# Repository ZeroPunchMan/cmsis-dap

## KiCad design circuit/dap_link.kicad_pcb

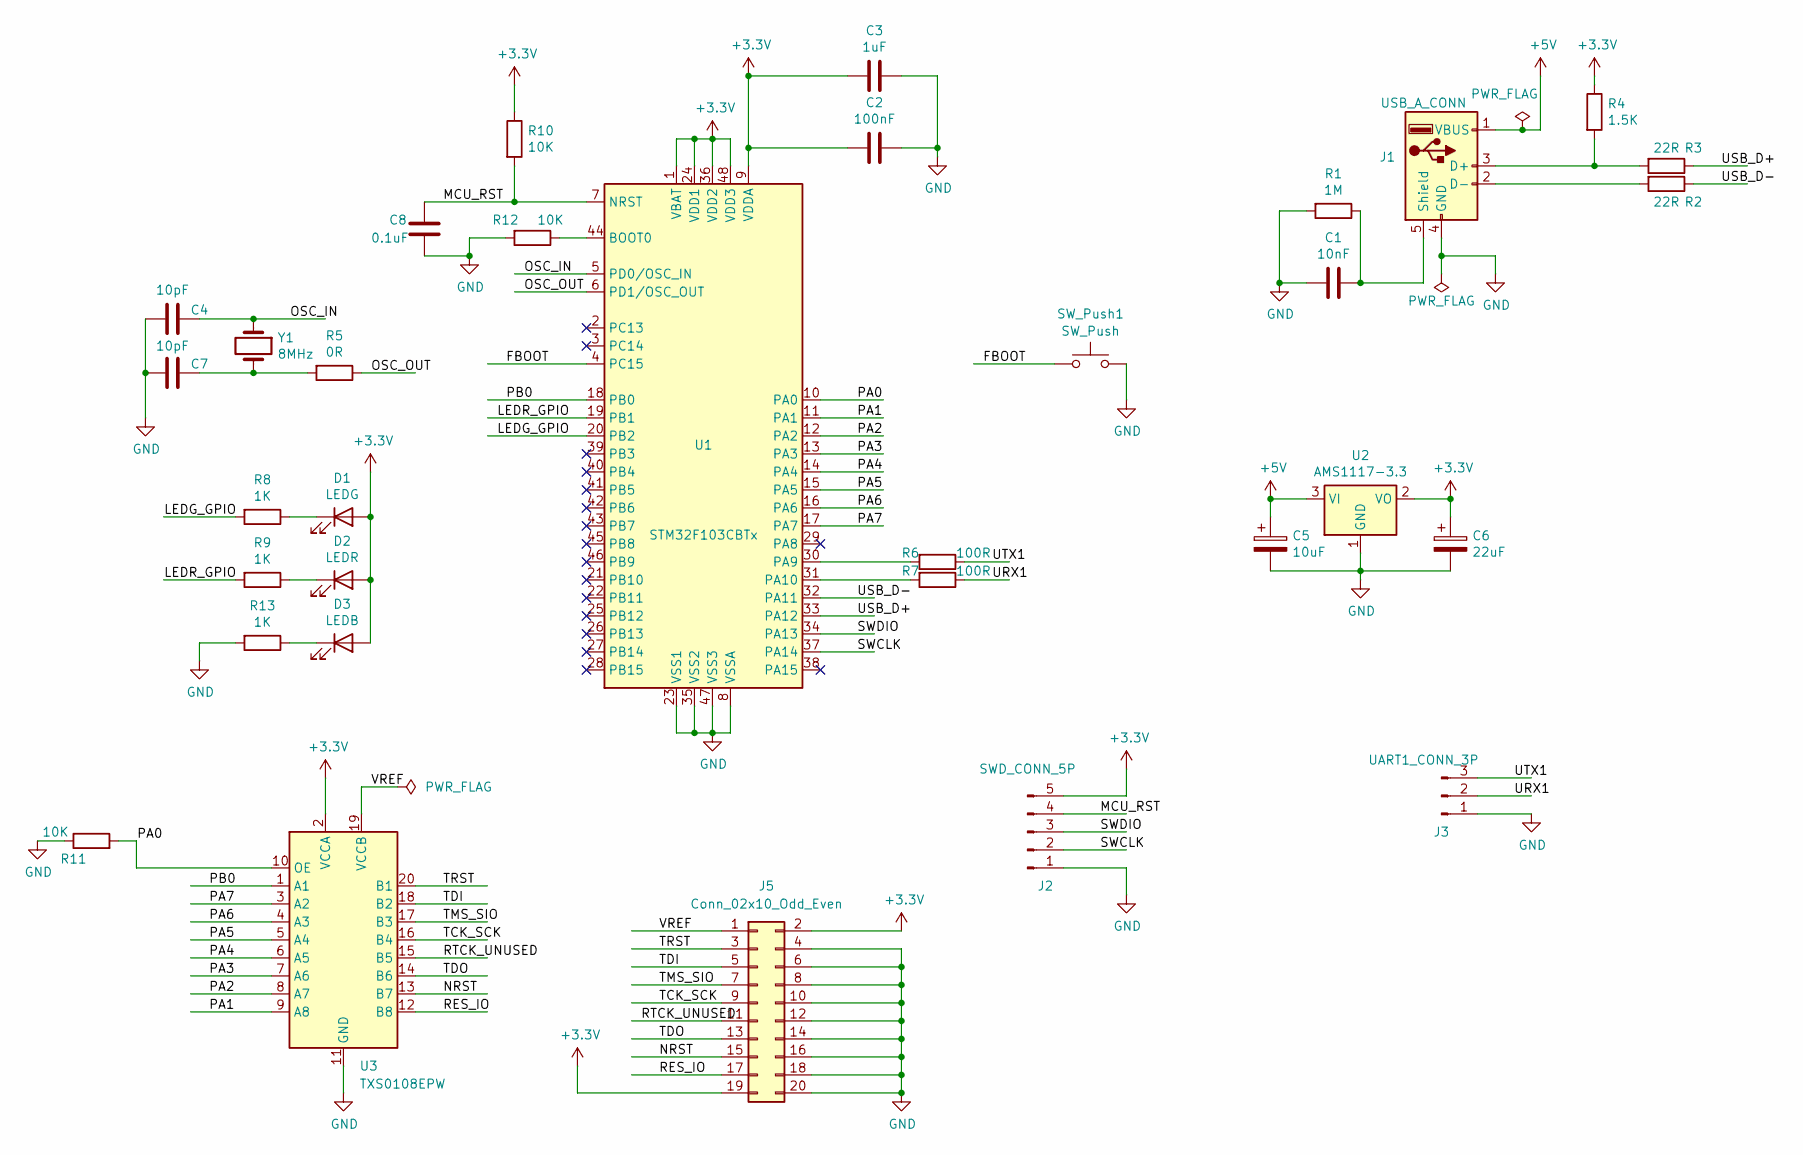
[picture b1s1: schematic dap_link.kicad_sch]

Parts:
C1: 10nF; C_0805_2012Metric_Pad1.18x1.45mm_HandSolder
C2: 100nF; C_0805_2012Metric_Pad1.18x1.45mm_HandSolder
C3: 1uF; C_0805_2012Metric_Pad1.18x1.45mm_HandSolder
C4, C7: 10pF; C_0805_2012Metric_Pad1.18x1.45mm_HandSolder
C5: 10uF; CP_EIA-3528-12_Kemet-T_Pad1.50x2.35mm_HandSolder
C6: 22uF; CP_EIA-3528-12_Kemet-T_Pad1.50x2.35mm_HandSolder
C8: 0.1uF; C_0805_2012Metric_Pad1.18x1.45mm_HandSolder
D1: LEDG; D_0805_2012Metric_Pad1.15x1.40mm_HandSolder
D2: LEDR; D_0805_2012Metric_Pad1.15x1.40mm_HandSolder
D3: LEDB; D_0805_2012Metric_Pad1.15x1.40mm_HandSolder
J1: USB_A_CONN; USB_A_CNCTech_1001-011-01101_Horizontal
J2: SWD_CONN_5P; PinHeader_1x05_P2.54mm_Vertical
J3: UART1_CONN_3P; PinHeader_1x03_P2.54mm_Vertical
J5: Conn_02x10_Odd_Even; PinSocket_2x10_P2.54mm_Vertical
R1: 1M; R_0805_2012Metric_Pad1.20x1.40mm_HandSolder
R2, R3: 22R; R_0805_2012Metric_Pad1.20x1.40mm_HandSolder
R4: 1.5K; R_0805_2012Metric_Pad1.20x1.40mm_HandSolder
R5: 0R; R_0805_2012Metric_Pad1.20x1.40mm_HandSolder
R6, R7: 100R; R_0805_2012Metric_Pad1.20x1.40mm_HandSolder
R8, R9, R13: 1K; R_0805_2012Metric_Pad1.20x1.40mm_HandSolder
R10, R11, R12: 10K; R_0805_2012Metric_Pad1.20x1.40mm_HandSolder
SW_Push1: SW_Push; SW_Push_1P1T_NO_6x6mm_H9.5mm
U1: STM32F103CBTx; LQFP-48_7x7mm_P0.5mm
U2: AMS1117-3.3; SOT-223-3_TabPin2
U3: TXS0108EPW; TSSOP-20_4.4x6.5mm_P0.65mm
Y1: 8MHz; Crystal_SMD_5032-2Pin_5.0x3.2mm_HandSoldering

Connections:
+3V3: C2.2, C3.2, C6.1, D1.2 (A), D2.2 (A), D3.2 (A), J2.5, J5.2, J5.19, R4.1, R10.1, U1.1 (VBAT), U1.9 (VDDA), U1.24 (VDD1), U1.36 (VDD2), U1.48 (VDD3), U2.2 (VO), U3.2 (VCCA)
+5V: C5.1, J1.1 (VBUS), U2.3 (VI)
/FBOOT: U1.4 (PC15); also elsewhere on the board
/LEDG_GPIO: R8.2, U1.20 (PB2)
/LEDR_GPIO: R9.2, U1.19 (PB1)
/MCU_RST: C8.1, J2.4, R10.2, U1.7 (NRST)
/NRST: J5.15, U3.13 (B7)
/OSC_IN: C4.1, U1.5 (PD0/OSC_IN), Y1.1
/OSC_OUT: R5.1, U1.6 (PD1/OSC_OUT)
/PA0: R11.2, U1.10 (PA0), U3.10 (OE)
/PA1: U1.11 (PA1), U3.9 (A8)
/PA2: U1.12 (PA2), U3.8 (A7)
/PA3: U1.13 (PA3), U3.7 (A6)
/PA4: U1.14 (PA4), U3.6 (A5)
/PA5: U1.15 (PA5), U3.5 (A4)
/PA6: U1.16 (PA6), U3.4 (A3)
/PA7: U1.17 (PA7), U3.3 (A2)
/PB0: U1.18 (PB0), U3.1 (A1)
/RES_IO: J5.17, U3.12 (B8)
/RTCK_UNUSED: J5.11, U3.15 (B5)
/SWCLK: J2.2, U1.37 (PA14)
/SWDIO: J2.3, U1.34 (PA13)
/TCK_SCK: J5.9, U3.16 (B4)
/TDI: J5.5, U3.18 (B2)
/TDO: J5.13, U3.14 (B6)
/TMS_SIO: J5.7, U3.17 (B3)
/TRST: J5.3, U3.20 (B1)
/URX1: J3.2, R7.1
/USB_D+: R3.1, U1.33 (PA12)
/USB_D-: R2.1, U1.32 (PA11)
/UTX1: J3.3, R6.1
/VREF: J5.1, U3.19 (VCCB)
GND: C1.2, C2.1, C3.1, C4.2, C5.2, C6.2, C7.2, C8.2, J1.4 (GND), J2.1, J3.1, J5.4, J5.6, J5.8, J5.10, J5.12, J5.14, J5.16, J5.18, J5.20, R1.2, R11.1, R12.2, R13.2, U1.8 (VSSA), U1.23 (VSS1), U1.35 (VSS2), U1.47 (VSS3), U2.1 (GND), U3.11 (GND); also elsewhere on the board
unnamed: C7.1, R5.2, Y1.2
unnamed: D1.1 (K), R8.1
unnamed: D2.1 (K), R9.1
unnamed: D3.1 (K), R13.1
unnamed: J1.3 (D+), R3.2, R4.2
unnamed: J1.2 (D-), R2.2
unnamed: C1.1, J1.5 (Shield), R1.1
unnamed: R12.1, U1.44 (BOOT0)
unnamed: R6.2, U1.30 (PA9)
unnamed: R7.2, U1.31 (PA10)

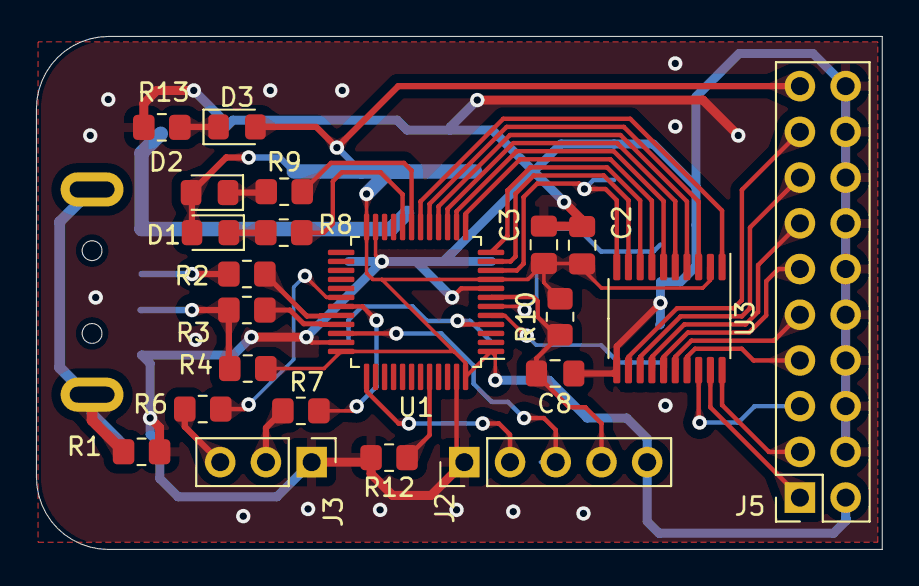
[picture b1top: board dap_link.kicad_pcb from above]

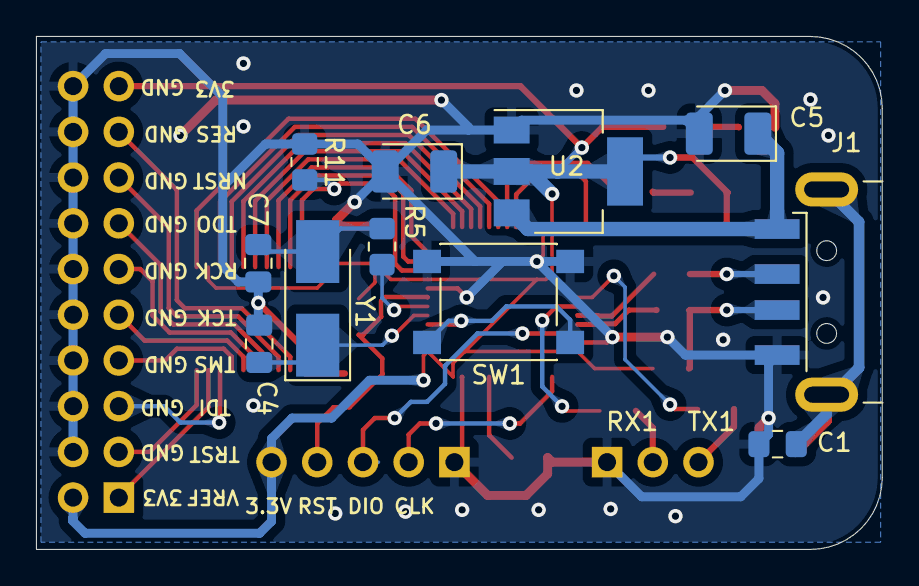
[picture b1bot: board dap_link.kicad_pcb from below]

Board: 2 copper layers, 47.0 x 28.5 mm, 33 parts (11 on the bottom side), 43 nets.

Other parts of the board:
SW1: SW_Push; SW_Push_1P1T_NO_6x6mm_H9.5mm

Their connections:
/FBOOT: SW1.1; also elsewhere on the board
GND: SW1.2; also elsewhere on the board

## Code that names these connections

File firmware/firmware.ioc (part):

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Mcu.Name=STM32F103C(8-B)Tx
Mcu.Package=LQFP48
Mcu.UserName=STM32F103C8Tx
PA10.Mode=Asynchronous
PA10.Signal=USART1_RX
PA11.Mode=Device
PA11.Signal=USB_DM
PA12.Mode=Device
PA12.Signal=USB_DP
PA13.Mode=Serial_Wire
PA13.Signal=SYS_JTMS-SWDIO
PA14.Mode=Serial_Wire
PA14.Signal=SYS_JTCK-SWCLK
PA7.Signal=GPIO_Output
PA8.Signal=GPIO_Output
PA9.Mode=Asynchronous
PA9.Signal=USART1_TX
PD0-OSC_IN.Mode=HSE-External-Oscillator
PD0-OSC_IN.Signal=RCC_OSC_IN
PD1-OSC_OUT.Mode=HSE-External-Oscillator
PD1-OSC_OUT.Signal=RCC_OSC_OUT
RCC.SYSCLKFreq_VALUE=48000000
RCC.SYSCLKSource=RCC_SYSCLKSOURCE_PLLCLK
board=custom

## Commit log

2022-02-19 clear
2022-03-26 USB ERROR
2022-03-27 usb start
2022-03-27 files exclude
2022-03-27 worked
2022-04-01 remove hs and ls desc
2022-04-04 xbox recognized
2022-04-04 diff in serial number
2022-04-04 endpoint how to user
2022-04-04 need adjust
2022-04-05 need higher freq
2022-04-05 datain not work
2022-04-06 360 need test
2022-04-06 360 button worked
2022-04-07 2 controller tested
2022-08-10 1.dap firmware update 2.add mutex and atomic uint
2022-08-11 rename usb class file
2022-08-12 dap usb, modified on hid
2022-08-12 add os descriptor
2022-08-12 usb pack size
2022-08-13 need dap process
2022-08-13 usb no data
2022-08-13 clib update
2022-08-15 enum ok
2022-09-01 dap not work
2022-09-02 swd error
2022-11-23 multibuff test not done
2022-12-03 mul buff tested
2022-12-07 cmd test failed
2022-12-12 jtag tested
2022-12-12 disable dap timestamp
2022-12-12 swd jtag tested
2023-02-12 fixed incompatible pointer type
2023-02-12 silent make
2023-03-30 systime update
2023-03-30 usb reset need test
2023-03-30 fix dap warning
2023-05-06 remove clib
2023-05-06 add new clib
2023-12-07 宏增加括号
2023-12-11 增加IO口注释
2023-12-11 新版kicad
2023-12-11 移除旧版kicad文件
2023-12-11 kicad有DRC错误
2023-12-11 DRC通过
2023-12-11 添加泪滴
2023-12-11 修改IO配置
2023-12-11 更新clib
2023-12-14 板子加OE下拉 IO初始化修改
2023-12-14 增加电源指示灯
2023-12-14 nrst改为推挽输出
2023-12-14 USB座子边距
2023-12-14 增加圆边
2023-12-14 接口增加一个3.3V
2023-12-14 增加丝印,缩小USB边距
2023-12-15 增加boot按钮
2023-12-15 更新丝印
